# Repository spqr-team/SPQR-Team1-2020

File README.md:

# SPQR1 Team 2020

SPQR1 Team 2020 Robot project repo, we are robot-makers based in ITIS G. Galilei Rome, currently competing in Soccer Lightweight league in RCJ.

Code found in master and mechanics and boards in branch hardware.

We are: 
  Davide Belli  [@DVDSpacca],
  Emanuele Coletta  [@EmaMaker],
  Marco De Amicis [@Morcock] and Siria Sannino  [@u-siri-ous].

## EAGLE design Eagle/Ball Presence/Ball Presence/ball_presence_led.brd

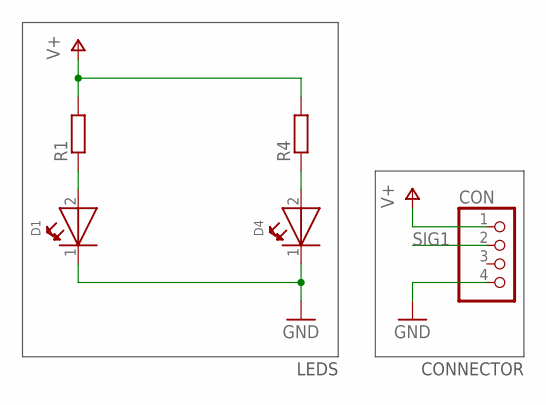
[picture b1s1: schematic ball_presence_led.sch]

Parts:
CON: PINHD-1X4; 1X04
D1, D4: WL-SMTW-150141AS73100-A; 3528-2PIN
R1, R4: R-EU_R0805; R0805

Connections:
GND: CON.4, D1.1 (K), D4.1 (K)
unnamed: D1.2 (A), R1.1
unnamed: D4.2 (A), R4.1
SIG1: CON.2
V+: CON.1, R1.2, R4.2

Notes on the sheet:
LEDS
CONNECTOR

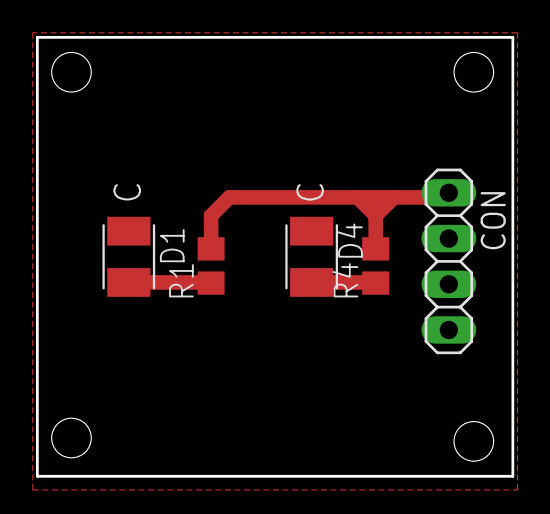
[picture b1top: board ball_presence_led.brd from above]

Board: 2 copper layers, 26.4 x 24.4 mm, 5 parts (0 on the bottom side), 4 nets.

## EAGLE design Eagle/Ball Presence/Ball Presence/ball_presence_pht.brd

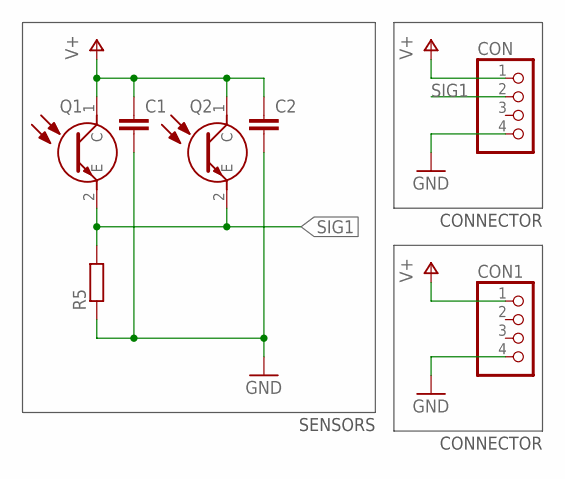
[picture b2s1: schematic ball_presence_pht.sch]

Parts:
C1, C2: C-EUC0805; C0805
CON, CON1: PINHD-1X4; 1X04
Q1, Q2: VEMT2520X01
R5: R-EU_R0805; R0805

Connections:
GND: C1.2, C2.2, CON.4, CON1.4, R5.1
SIG1: CON.2, Q1.2 (E), Q2.2 (E), R5.2
V+: C1.1, C2.1, CON.1, CON1.1, Q1.1 (C), Q2.1 (C)

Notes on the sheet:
SENSORS
CONNECTOR

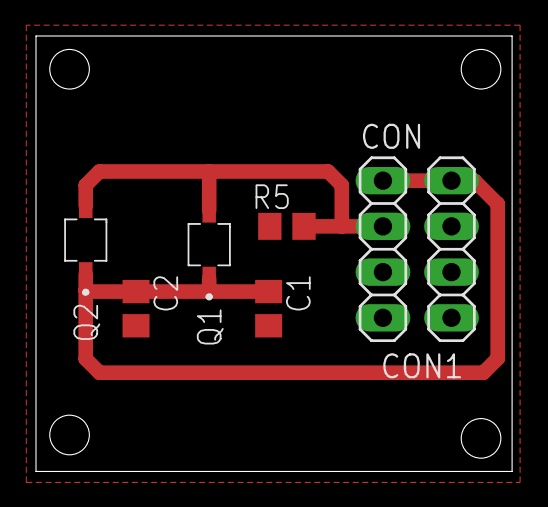
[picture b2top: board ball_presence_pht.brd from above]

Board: 2 copper layers, 26.4 x 24.2 mm, 7 parts (0 on the bottom side), 3 nets.

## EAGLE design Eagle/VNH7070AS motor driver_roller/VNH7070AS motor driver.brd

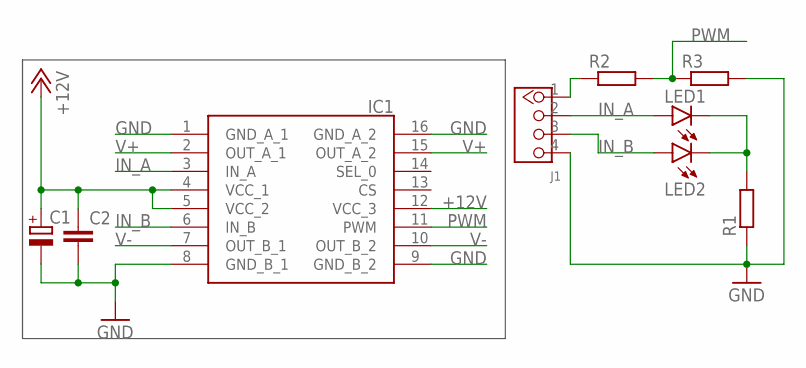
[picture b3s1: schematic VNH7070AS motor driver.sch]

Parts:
C1: CPOL-EUCT7343; CT7343
C2: C-EUC0805; C0805
IC1: VNH7070ASTR; SOIC127P600X175-16N
J1: TWIG_2.0; 2.0_1X4
LED1, LED2: LEDCHIPLED_1206; CHIPLED_1206
R1, R2, R3: R-EU_R0805; R0805

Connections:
+12V: C1.+, C2.1, IC1.4 (VCC_1), IC1.5 (VCC_2), IC1.12 (VCC_3)
GND: C1.-, C2.2, IC1.1 (GND_A_1), IC1.8 (GND_B_1), IC1.9 (GND_B_2), IC1.16 (GND_A_2), J1.4, R1.1, R3.2
IN_A: IC1.3 (IN_A), J1.2, LED1.A
IN_B: IC1.6 (IN_B), J1.3, LED2.A
unnamed: J1.1, R2.1
unnamed: LED1.C, LED2.C, R1.2
PWM: IC1.11 (PWM), R2.2, R3.1
V+: IC1.2 (OUT_A_1), IC1.15 (OUT_A_2)
V-: IC1.7 (OUT_B_1), IC1.10 (OUT_B_2)

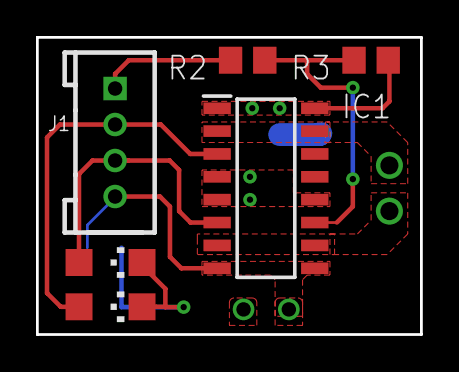
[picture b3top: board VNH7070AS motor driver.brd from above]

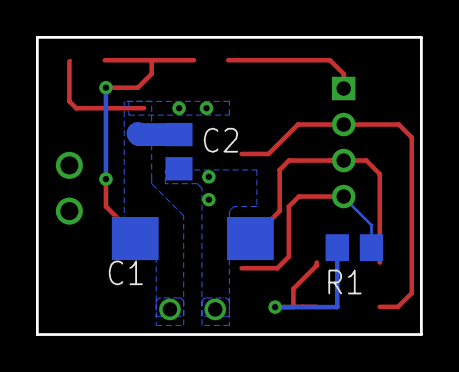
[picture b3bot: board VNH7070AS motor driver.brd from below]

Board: 2 copper layers, 21.3 x 16.5 mm, 9 parts (3 on the bottom side), 9 nets.

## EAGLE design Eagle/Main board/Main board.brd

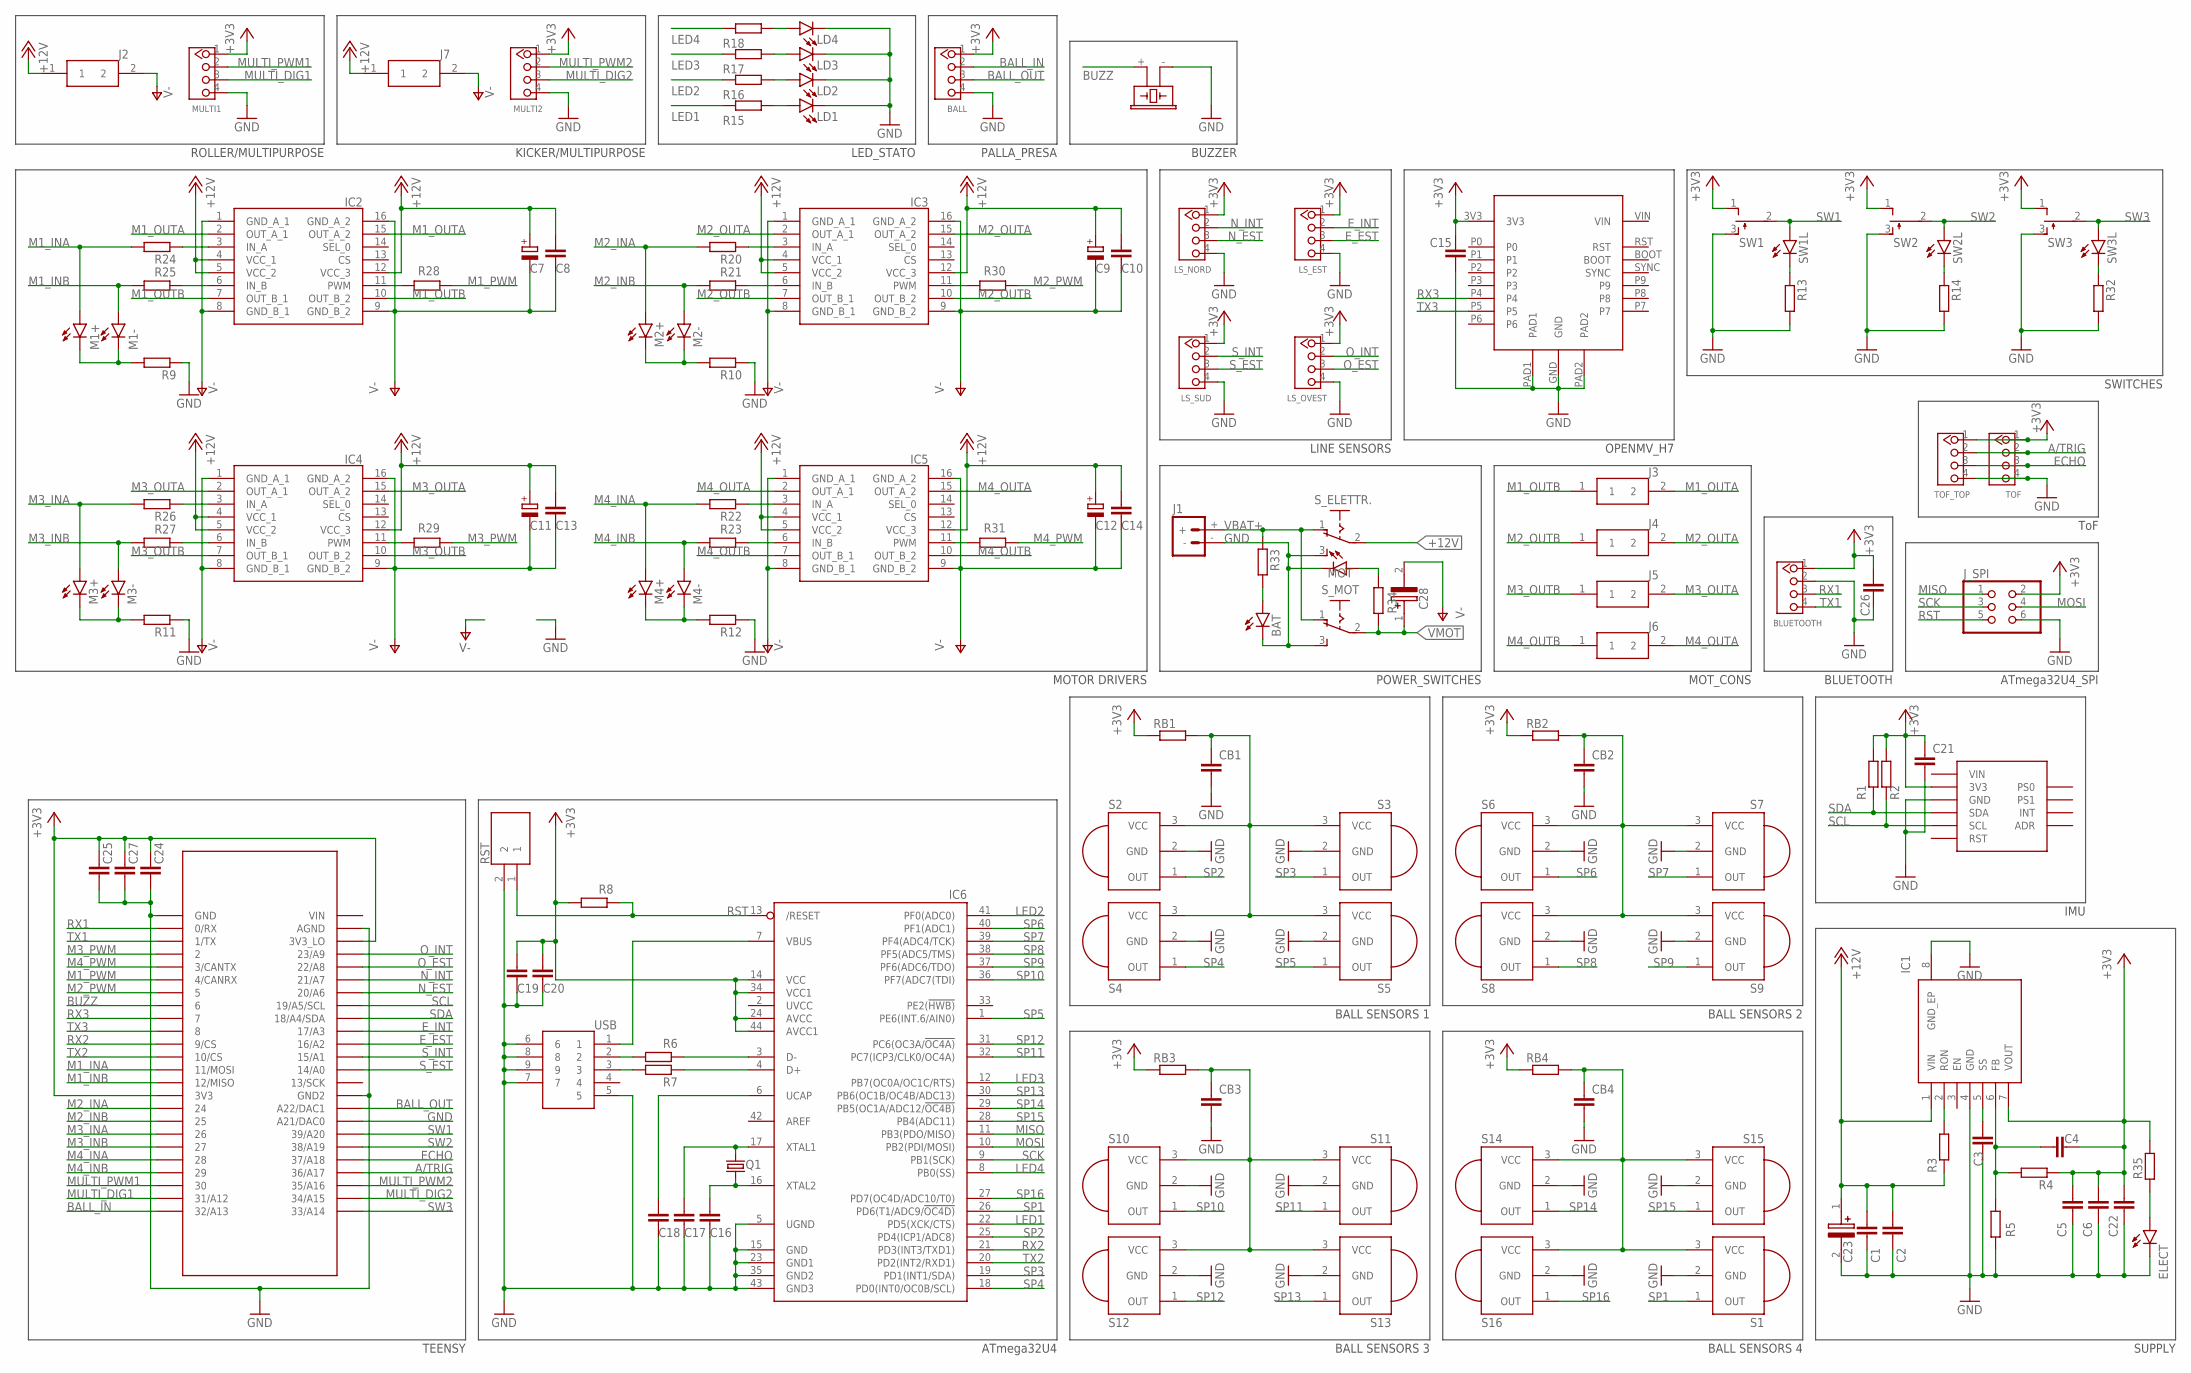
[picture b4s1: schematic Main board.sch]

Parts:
BALL: TWIG_2.0; 2.0_1X4
BAT: LEDCHIPLED_1206; CHIPLED_1206
BLUETOOTH: TWIG_2.0; 2.0_1X4
BUZZER: F/CM12P
C1, C2, C22, C24, C27: 100n; C0805
C3, C4: 22n; C0805
C5, C6: 100u; C1206
C7: 1OOu; PANASONIC_E
C8, C10, C13, C14, C15, C16, C17, C18, C20, C21, C26: 1u; C0805
C9, C11, C12: 100u; PANASONIC_E
C19: 1u; C1206
C23, C28: EEV-FK1C152Q; FKV(H13)
C25: 100n; C1206
CB1, CB2, CB3, CB4: 0.1uF; C0805
ELECT: LEDCHIPLED_1206; CHIPLED_1206
IC1: LMZ14202TZE-ADJ_NOPB; NDW0007A
IC2, IC3, IC4, IC5: VNH7070ASTR; SOIC127P600X175-16N
IC6: ATMEGA32U4-AU; TQFP44
J1: BATTERY_CONN_DEANS; DEANS
J2, J3, J4, J5, J6, J7: 43650-0201; 43650-0200
J_SPI: PINHD-2X3; 2X03
LD1, LD2, LD3, LD4: LEDCHIPLED_1206; CHIPLED_1206
LS_EST: TWIG_2.0; 2.0_1X4
LS_NORD: TWIG_2.0; 2.0_1X4
LS_OVEST: TWIG_2.0; 2.0_1X4
LS_SUD: TWIG_2.0; 2.0_1X4
M1+, M1-, M2+, M2-, M3+, M3-, M4+, M4-: LEDCHIPLED_1206; CHIPLED_1206
MOT: LEDCHIPLED_1206; CHIPLED_1206
MULTI1, MULTI2: TWIG_2.0; 2.0_1X4
Q1: CRYSTALHC49UP; HC49UP
R1, R2: 10k; R0805
R3: 61,9k; R0805
R4: 3,32k; R0805
R5: 1,07k; R0805
R6, R7, R8, R9, R10, R11, R12, R13, R14, R15, R16, R17, R18, R20, R21, R22, R23, R24, R25, R26, R27, R28, R29, R30, R31, R32, R33, R34, R35: R-EU_R0805; R0805
RB1, RB2, RB3, RB4: 22; R0805
RST: KSR231GLFS; KSR
S1, S2, S3, S4, S5, S6, S7, S8, S9, S10, S11, S12, S13, S14, S15, S16: PNA460XM
SW1, SW2, SW3: TL38PO; TL3XPO
SW1L, SW2L, SW3L: LEDCHIPLED_1206; CHIPLED_1206
S_ELETTR.: 255SB
S_MOT: 255SB
TOF: TWIG_2.0; 2.0_1X4
TOF_TOP: TWIG_2.0; 2.0_1X4
U$1: TEENSY_3.5/3.6
U$2: OPENMV_H7
U$4: BNO055
USB: 10104111-0001LF; 101041110001LF

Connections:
+3V3: BALL.1, BLUETOOTH.1, C4.2, C5.1, C6.1, C15.1, C19.1, C20.1, C21.1, C22.1, C24.1, C25.1, C26.1, C27.1, IC1.7 (VOUT), IC6.14 (VCC), IC6.24 (AVCC), IC6.34 (VCC1), IC6.44 (AVCC1), J_SPI.2, LS_EST.1, LS_NORD.1, LS_OVEST.1, LS_SUD.1, MULTI1.1, MULTI2.1, R1.2, R2.2, R4.1, R8.2, R35.2, RB1.1, RB2.1, RB3.1, RB4.1, SW1.1 (O), SW2.1 (O), SW3.1 (O), TOF.1, TOF_TOP.1, U$1.3V3, U$1.3V3_LO, U$2.3V3, U$4.3V3
+12V: C1.1, C2.1, C23.1 (+), IC1.1 (VIN), R3.1, S_ELETTR..2
A/TRIG: TOF.2, TOF_TOP.2, U$1.36/A17
BALL_IN: BALL.2, U$1.32/A13
BALL_OUT: BALL.3, U$1.A22/DAC1
BUZZ: BUZZER.+ (1), U$1.6
ECHO: TOF.3, TOF_TOP.3, U$1.37/A18
E_EST: LS_EST.3, U$1.16/A2
E_INT: LS_EST.2, U$1.17/A3
GND: BALL.4, BAT.C, BLUETOOTH.2, BUZZER.- (2), C1.2, C2.2, C3.2, C5.2, C6.2, C15.2, C16.2, C17.2, C18.2, C19.2, C20.2, C21.2, C22.2, C23.2 (-), C24.2, C25.2, C26.2, C27.2, CB1.2, CB2.2, CB3.2, CB4.2, ELECT.C, IC1.4 (GND), IC1.8 (GND_EP), IC6.5 (UGND), IC6.15 (GND), IC6.23 (GND1), IC6.35 (GND2), IC6.43 (GND3), J1.-, J_SPI.6, LD1.C, LD2.C, LD3.C, LD4.C, LS_EST.4, LS_NORD.4, LS_OVEST.4, LS_SUD.4, MOT.C, MULTI1.4, MULTI2.4, R5.1, R9.1, R10.1, R11.1, R12.1, R13.2, R14.2, R32.2, RST.2, S1.2 (GND), S2.2 (GND), S3.2 (GND), S4.2 (GND), S5.2 (GND), S6.2 (GND), S7.2 (GND), S8.2 (GND), S9.2 (GND), S10.2 (GND), S11.2 (GND), S12.2 (GND), S13.2 (GND), S14.2 (GND), S15.2 (GND), S16.2 (GND), SW1.3 (S), SW2.3 (S), SW3.3 (S), S_ELETTR..3 (S), S_MOT.3 (S), TOF.4, TOF_TOP.4, U$1.21/DAC0 (A21/DAC0), U$1.AGND, U$1.GND, U$1.GND2, U$2.GND, U$2.PAD1, U$2.PAD2, U$4.GND, USB.5, USB.6, USB.7, USB.8, USB.9; also elsewhere on the board
INA_1: IC2.3 (IN_A), R24.1
INA_2: IC3.3 (IN_A), R20.1
INA_3: IC4.3 (IN_A), R26.1
INA_4: IC5.3 (IN_A), R22.1
INB_1: IC2.6 (IN_B), R25.1
INB_2: IC3.6 (IN_B), R21.1
INB_3: IC4.6 (IN_B), R27.1
INB_4: IC5.6 (IN_B), R23.1
LED1: IC6.22 (PD5(XCK/CTS)), R15.1
LED2: IC6.41 (PF0(ADC0)), R16.1
LED3: IC6.12 (PB7(OC0A/OC1C/RTS)), R17.1
LED4: IC6.8 (PB0(SS)), R18.1
M1_INA: M1+.A, R24.2, U$1.11/MOSI
M1_INB: M1-.A, R25.2, U$1.12/MISO
M1_OUTA: IC2.2 (OUT_A_1), IC2.15 (OUT_A_2), J3.2
M1_OUTB: IC2.7 (OUT_B_1), IC2.10 (OUT_B_2), J3.1
M1_PWM: R28.1, U$1.4/CANRX
M2_INA: M2+.A, R20.2, U$1.24
M2_INB: M2-.A, R21.2, U$1.25
M2_OUTA: IC3.2 (OUT_A_1), IC3.15 (OUT_A_2), J4.2
M2_OUTB: IC3.7 (OUT_B_1), IC3.10 (OUT_B_2), J4.1
M2_PWM: R30.1, U$1.5
M3_INA: M3+.A, R26.2, U$1.26
M3_INB: M3-.A, R27.2, U$1.27
M3_OUTA: IC4.2 (OUT_A_1), IC4.15 (OUT_A_2), J5.2
M3_OUTB: IC4.7 (OUT_B_1), IC4.10 (OUT_B_2), J5.1
M3_PWM: R29.1, U$1.2
M4_INA: M4+.A, R22.2, U$1.28
M4_INB: M4-.A, R23.2, U$1.29
M4_OUTA: IC5.2 (OUT_A_1), IC5.15 (OUT_A_2), J6.2
M4_OUTB: IC5.7 (OUT_B_1), IC5.10 (OUT_B_2), J6.1
M4_PWM: R31.1, U$1.3/CANTX
MISO: IC6.11 (PB3(PDO/MISO)), J_SPI.1
MOSI: IC6.10 (PB2(PDI/MOSI)), J_SPI.4
MULTI_DIG1: MULTI1.3, U$1.31/A12
MULTI_DIG2: MULTI2.3, U$1.34/A15
MULTI_PWM1: MULTI1.2, U$1.30
MULTI_PWM2: MULTI2.2, U$1.35/A16
unnamed: IC1.2 (RON), R3.2
unnamed: C4.1, IC1.6 (FB), R4.2, R5.2
unnamed: C3.1, IC1.5 (SS)
unnamed: LD4.A, R18.2
unnamed: C17.1, IC6.17 (XTAL1), Q1.2
unnamed: C16.1, IC6.16 (XTAL2), Q1.1
unnamed: C18.1, IC6.6 (UCAP)
unnamed: IC6.3 (D-), R6.1
unnamed: R6.2, USB.2
unnamed: R7.2, USB.3
unnamed: IC6.4 (D+), R7.1
unnamed: IC6.7 (VBUS), USB.1
unnamed: M2+.C, M2-.C, R10.2
unnamed: M1+.C, M1-.C, R9.2
unnamed: M3+.C, M3-.C, R11.2
unnamed: M4+.C, M4-.C, R12.2
unnamed: R13.1, SW1L.C
unnamed: R14.1, SW2L.C
unnamed: R32.1, SW3L.C
unnamed: LD1.A, R15.2
unnamed: LD2.A, R16.2
unnamed: LD3.A, R17.2
unnamed: BAT.A, R33.2
unnamed: MOT.A, R34.2
unnamed 73: ELECT.A, R35.1; also elsewhere on the board
N_EST: LS_NORD.3, U$1.20/A6
N_INT: LS_NORD.2, U$1.21/A7
O_EST: LS_OVEST.3, U$1.22/A8
O_INT: LS_OVEST.2, U$1.23/A9
POWER_BLOCK_1: CB1.1, RB1.2, S2.3 (VCC), S3.3 (VCC), S4.3 (VCC), S5.3 (VCC)
POWER_BLOCK_2: CB2.1, RB2.2, S6.3 (VCC), S7.3 (VCC), S8.3 (VCC), S9.3 (VCC)
POWER_BLOCK_3: CB3.1, RB3.2, S10.3 (VCC), S11.3 (VCC), S12.3 (VCC), S13.3 (VCC)
POWER_BLOCK_4: CB4.1, RB4.2, S1.3 (VCC), S14.3 (VCC), S15.3 (VCC), S16.3 (VCC)
PWM3: IC4.11 (PWM), R29.2
PWM_1: IC2.11 (PWM), R28.2
PWM_2: IC3.11 (PWM), R30.2
PWM_4: IC5.11 (PWM), R31.2
RST: IC6.13 (/RESET), J_SPI.5, R8.1, RST.1
RX1: BLUETOOTH.3, U$1.0/RX
RX2: IC6.21 (PD3(INT3/TXD1)), U$1.9/CS
RX3: U$1.7, U$2.P4
SCK: IC6.9 (PB1(SCK)), J_SPI.3
SCL: R2.1, U$1.19/A5/SCL, U$4.SCL
SDA: R1.1, U$1.18/A4/SDA, U$4.SDA
SP1: IC6.26 (PD6(T1/ADC9/!OC4D)), S1.1 (OUT)
SP2: IC6.25 (PD4(ICP1/ADC8)), S2.1 (OUT)
SP3: IC6.19 (PD1(INT1/SDA)), S3.1 (OUT)
SP4: IC6.18 (PD0(INT0/OC0B/SCL)), S4.1 (OUT)
SP5: IC6.1 (PE6(INT.6/AIN0)), S5.1 (OUT)
SP6: IC6.40 (PF1(ADC1)), S6.1 (OUT)
SP7: IC6.39 (PF4(ADC4/TCK)), S7.1 (OUT)
SP8: IC6.38 (PF5(ADC5/TMS)), S8.1 (OUT)
SP9: IC6.37 (PF6(ADC6/TDO)), S9.1 (OUT)
SP10: IC6.36 (PF7(ADC7(TDI)), S10.1 (OUT)
SP11: IC6.32 (PC7(ICP3/CLK0/OC4A)), S11.1 (OUT)
SP12: IC6.31 (PC6(OC3A/!OC4A)), S12.1 (OUT)
SP13: IC6.30 (PB6(OC1B/OC4B/ADC13)), S13.1 (OUT)
SP14: IC6.29 (PB5(OC1A/ADC12/!OC4B)), S14.1 (OUT)
SP15: IC6.28 (PB4(ADC11)), S15.1 (OUT)
SP16: IC6.27 (PD7(OC4D/ADC10/T0)), S16.1 (OUT)
SW1: SW1.2, SW1L.A, U$1.39/A20
SW2: SW2.2, SW2L.A, U$1.38/A19
SW3: SW3.2, SW3L.A, U$1.33/A14
S_EST: LS_SUD.3, U$1.14/A0
S_INT: LS_SUD.2, U$1.15/A1
TX1: BLUETOOTH.4, U$1.1/TX
TX2: IC6.20 (PD2(INT2/RXD1)), U$1.10/CS
TX3: U$1.8, U$2.P5
V-: C7.-, C8.2, C9.-, C10.2, C11.-, C12.-, C13.2, C14.2, C28.2 (-), IC2.1 (GND_A_1), IC2.8 (GND_B_1), IC2.9 (GND_B_2), IC2.16 (GND_A_2), IC3.1 (GND_A_1), IC3.8 (GND_B_1), IC3.9 (GND_B_2), IC3.16 (GND_A_2), IC4.1 (GND_A_1), IC4.8 (GND_B_1), IC4.9 (GND_B_2), IC4.16 (GND_A_2), IC5.1 (GND_A_1), IC5.8 (GND_B_1), IC5.9 (GND_B_2), IC5.16 (GND_A_2), J2.2, J7.2
VBAT+: J1.+, R33.1, S_ELETTR..1 (O), S_MOT.1 (O)
VMOT: C7.+, C8.1, C9.+, C10.1, C11.+, C12.+, C13.1, C14.1, C28.1 (+), IC2.4 (VCC_1), IC2.5 (VCC_2), IC2.12 (VCC_3), IC3.4 (VCC_1), IC3.5 (VCC_2), IC3.12 (VCC_3), IC4.4 (VCC_1), IC4.5 (VCC_2), IC4.12 (VCC_3), IC5.4 (VCC_1), IC5.5 (VCC_2), IC5.12 (VCC_3), J2.1, J7.1, R34.1, S_MOT.2

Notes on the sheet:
TEENSY
IMU
SUPPLY
POWER_SWITCHES
BALL SENSORS 1
BALL SENSORS 2
BALL SENSORS 3
BALL SENSORS 4
LINE SENSORS
MOTOR DRIVERS
OPENMV_H7
ATmega32U4
ATmega32U4_SPI
SWITCHES
BUZZER
LED_STATO
MOT_CONS
BLUETOOTH
ToF
ROLLER/MULTIPURPOSE
KICKER/MULTIPURPOSE
PALLA_PRESA

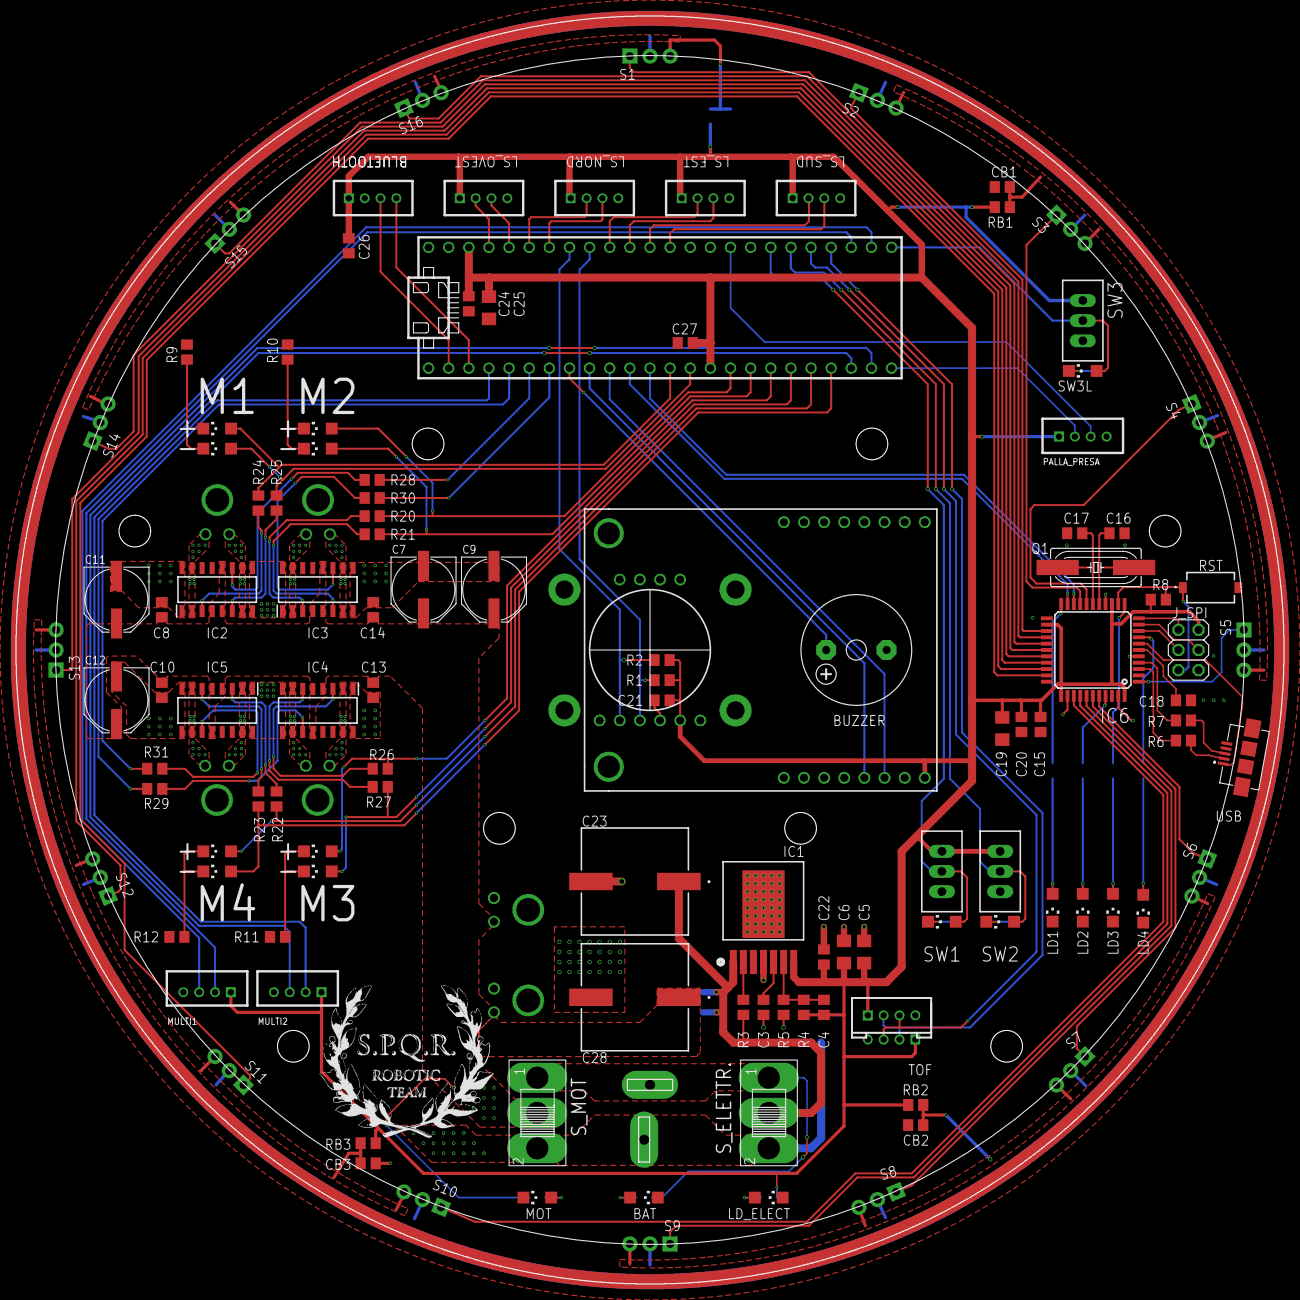
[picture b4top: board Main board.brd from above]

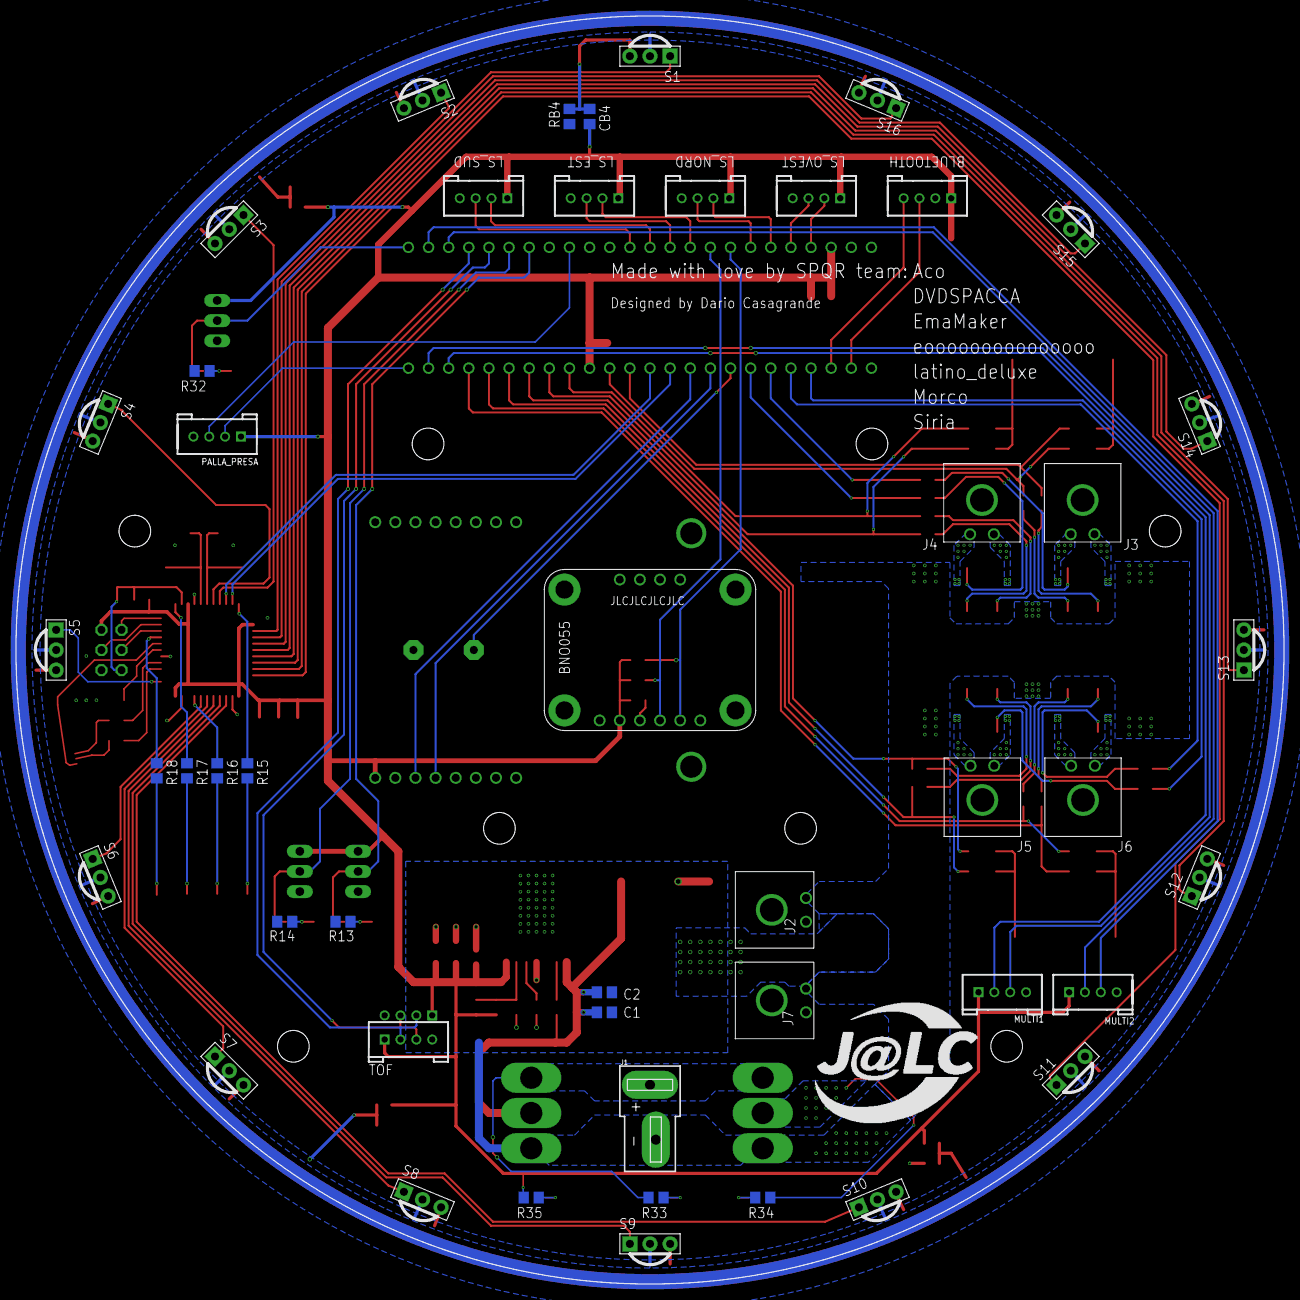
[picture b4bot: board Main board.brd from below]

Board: 2 copper layers, 160.0 x 160.0 mm, 140 parts (47 on the bottom side), 119 nets.

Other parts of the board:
LD_ELECT: CHIPLED_1206

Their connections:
GND: LD_ELECT.C; also elsewhere on the board
unnamed 73: LD_ELECT.A; also elsewhere on the board

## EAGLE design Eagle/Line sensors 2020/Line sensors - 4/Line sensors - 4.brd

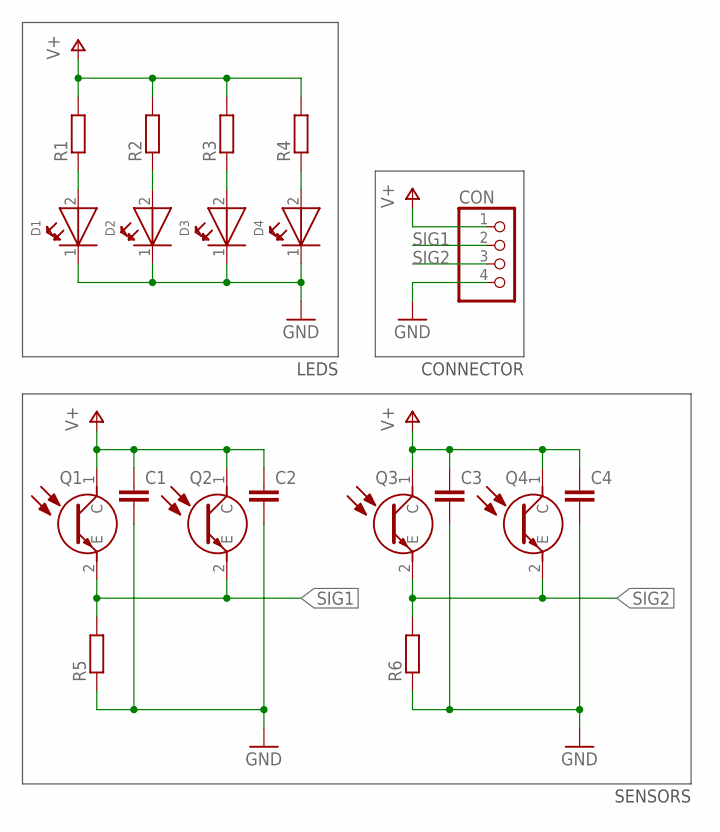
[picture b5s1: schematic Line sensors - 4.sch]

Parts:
C1, C2, C3, C4: C-EUC0805; C0805
CON: PINHD-1X4; 1X04
D1, D2, D3, D4: WL-SMTW-150141AS73100-A; 3528-2PIN
Q1, Q2, Q3, Q4: VEMT2520X01
R1, R2, R3, R4, R5, R6: R-EU_R0805; R0805

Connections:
GND: C1.2, C2.2, C3.2, C4.2, CON.4, D1.1 (K), D2.1 (K), D3.1 (K), D4.1 (K), R5.1, R6.1; also elsewhere on the board
unnamed: D1.2 (A), R1.1
unnamed: D2.2 (A), R2.1
unnamed: D3.2 (A), R3.1
unnamed: D4.2 (A), R4.1
SIG1: CON.2, Q1.2 (E), Q2.2 (E), R5.2; also elsewhere on the board
SIG2: CON.3, Q3.2 (E), Q4.2 (E), R6.2; also elsewhere on the board
V+: C1.1, C2.1, C3.1, C4.1, CON.1, Q1.1 (C), Q2.1 (C), Q3.1 (C), Q4.1 (C), R1.2, R2.2, R3.2, R4.2; also elsewhere on the board

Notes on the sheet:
SENSORS
LEDS
CONNECTOR

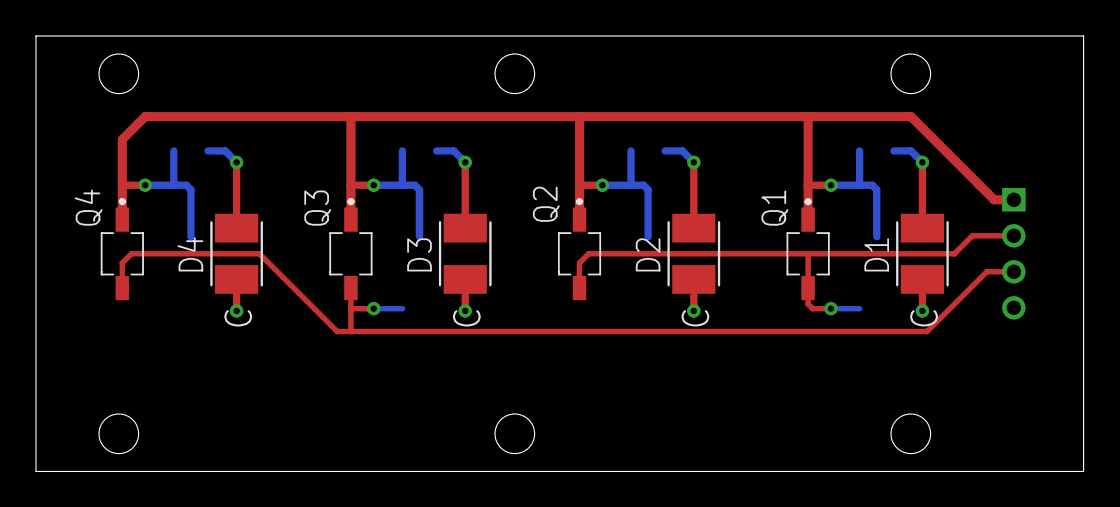
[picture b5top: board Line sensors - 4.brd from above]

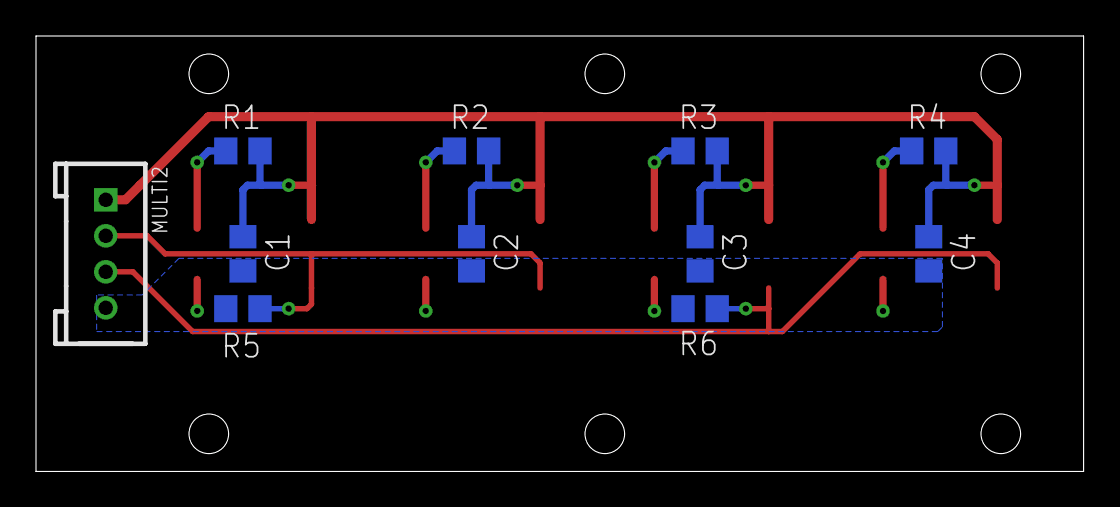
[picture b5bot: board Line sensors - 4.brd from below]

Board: 2 copper layers, 58.2 x 24.2 mm, 19 parts (11 on the bottom side), 8 nets.

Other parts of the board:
MULTI2: TWIG_2.0; 2.0_1X4

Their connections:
GND: MULTI2.4; also elsewhere on the board
SIG1: MULTI2.2; also elsewhere on the board
SIG2: MULTI2.3; also elsewhere on the board
V+: MULTI2.1; also elsewhere on the board

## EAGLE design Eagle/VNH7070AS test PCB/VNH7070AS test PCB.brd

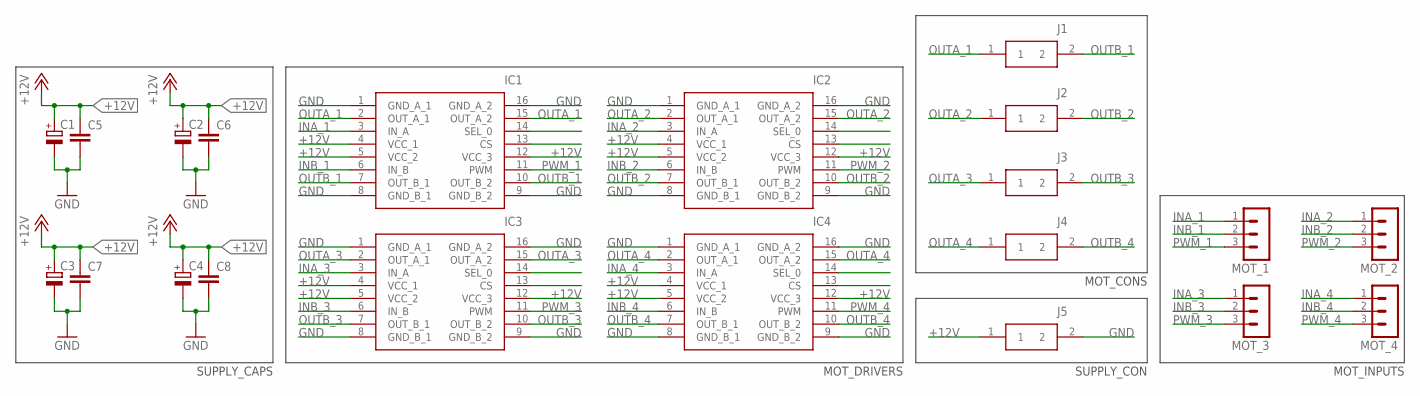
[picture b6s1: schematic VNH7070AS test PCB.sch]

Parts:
C1, C2, C3, C4: 220uF; E3,5-8
C5, C6, C7, C8: 100nF; C1206
IC1, IC2, IC3, IC4: VNH7070ASTR; SOIC127P600X175-16N
J1, J2, J3, J4, J5: 70553-0001; SHDRRA2W109P0_254_1X2_762X1359
MOT_1, MOT_2, MOT_3, MOT_4: MA03-1

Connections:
+12V: C1.+, C2.+, C3.+, C4.+, C5.1, C6.1, C7.1, C8.1, IC1.4 (VCC_1), IC1.5 (VCC_2), IC1.12 (VCC_3), IC2.4 (VCC_1), IC2.5 (VCC_2), IC2.12 (VCC_3), IC3.4 (VCC_1), IC3.5 (VCC_2), IC3.12 (VCC_3), IC4.4 (VCC_1), IC4.5 (VCC_2), IC4.12 (VCC_3), J5.1
GND: C1.-, C2.-, C3.-, C4.-, C5.2, C6.2, C7.2, C8.2, IC1.1 (GND_A_1), IC1.8 (GND_B_1), IC1.9 (GND_B_2), IC1.16 (GND_A_2), IC2.1 (GND_A_1), IC2.8 (GND_B_1), IC2.9 (GND_B_2), IC2.16 (GND_A_2), IC3.1 (GND_A_1), IC3.8 (GND_B_1), IC3.9 (GND_B_2), IC3.16 (GND_A_2), IC4.1 (GND_A_1), IC4.8 (GND_B_1), IC4.9 (GND_B_2), IC4.16 (GND_A_2), J5.2
INA_1: IC1.3 (IN_A), MOT_1.1
INA_2: IC2.3 (IN_A), MOT_2.1
INA_3: IC3.3 (IN_A), MOT_3.1
INA_4: IC4.3 (IN_A), MOT_4.1
INB_1: IC1.6 (IN_B), MOT_1.2
INB_2: IC2.6 (IN_B), MOT_2.2
INB_3: IC3.6 (IN_B), MOT_3.2
INB_4: IC4.6 (IN_B), MOT_4.2
OUTA_1: IC1.2 (OUT_A_1), IC1.15 (OUT_A_2), J1.1
OUTA_2: IC2.2 (OUT_A_1), IC2.15 (OUT_A_2), J2.1
OUTA_3: IC3.2 (OUT_A_1), IC3.15 (OUT_A_2), J3.1
OUTA_4: IC4.2 (OUT_A_1), IC4.15 (OUT_A_2), J4.1
OUTB_1: IC1.7 (OUT_B_1), IC1.10 (OUT_B_2), J1.2
OUTB_2: IC2.7 (OUT_B_1), IC2.10 (OUT_B_2), J2.2
OUTB_3: IC3.7 (OUT_B_1), IC3.10 (OUT_B_2), J3.2
OUTB_4: IC4.7 (OUT_B_1), IC4.10 (OUT_B_2), J4.2
PWM_1: IC1.11 (PWM), MOT_1.3
PWM_2: IC2.11 (PWM), MOT_2.3
PWM_3: IC3.11 (PWM), MOT_3.3
PWM_4: IC4.11 (PWM), MOT_4.3

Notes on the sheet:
SUPPLY_CAPS
MOT_DRIVERS
MOT_CONS
SUPPLY_CON
MOT_INPUTS

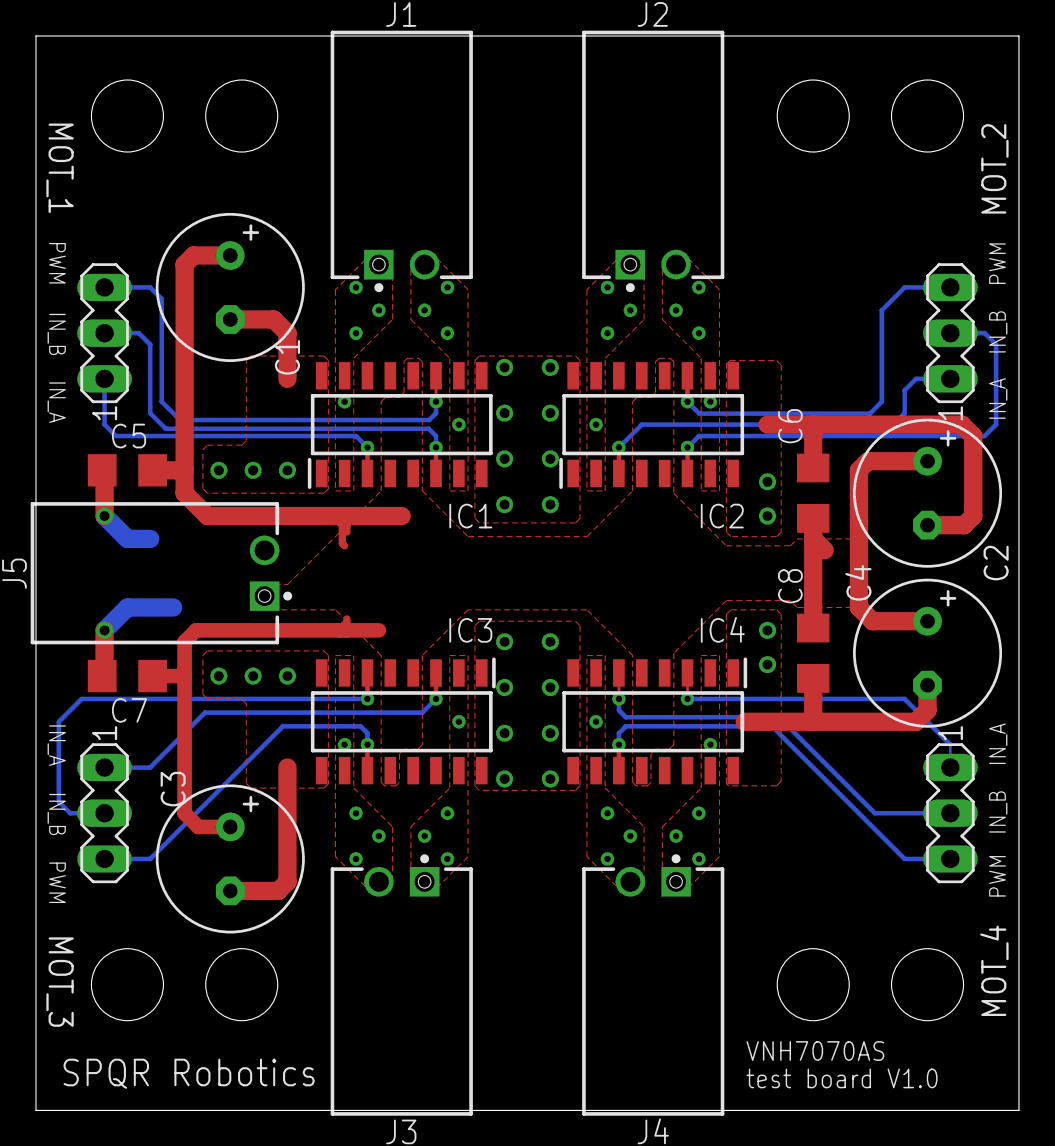
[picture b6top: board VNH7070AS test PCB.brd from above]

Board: 2 copper layers, 54.6 x 59.7 mm, 21 parts (0 on the bottom side), 22 nets.

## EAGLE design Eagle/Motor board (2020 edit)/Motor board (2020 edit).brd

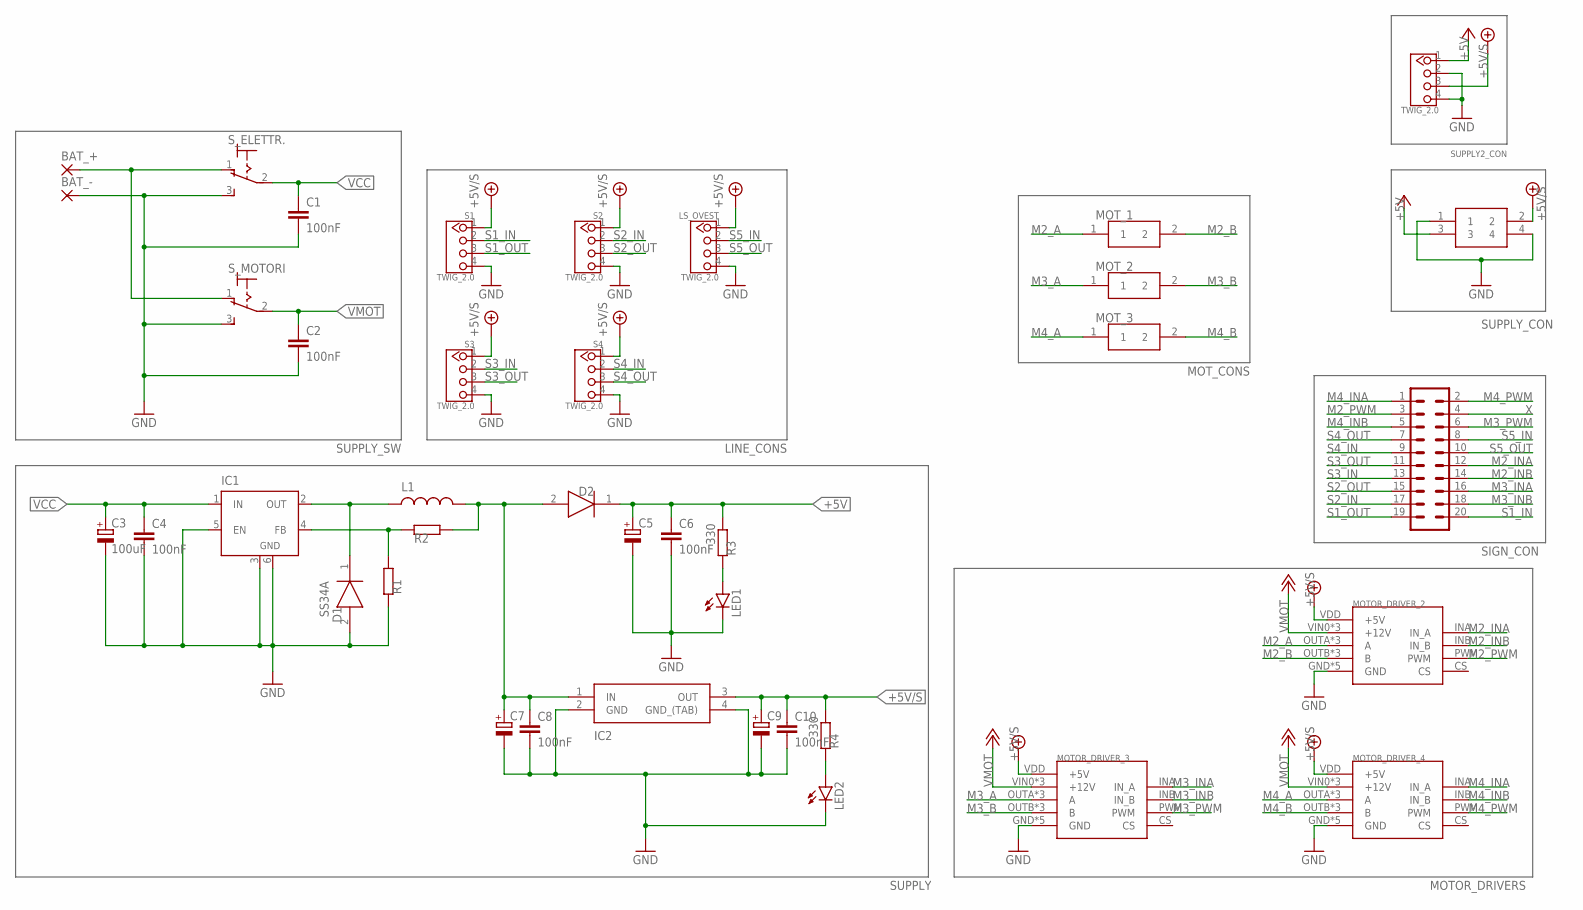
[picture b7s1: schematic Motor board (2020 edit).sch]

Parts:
BAT_+: 3,81/1,4
BAT_-: 3,81/1,4
C1, C2, C4, C6, C8, C10: 100nF; C1206
C3: 100uF; CT7343
C5, C7, C9: CPOL-EUE; PANASONIC_E
D1: SS34A; DIOM5026X262N
D2: SE20FG-M3_H; SODFL3718X108N
IC1: LM2596S; TO263-5
IC2: LM2940CS-5.0_NOPB; TO254P1435X464-4N
L1: 47uH; MSS1260
LED1, LED2: LEDSML1206; SML1206
LS_OVEST: TWIG_2.0; 2.0_1X4
MOTOR_DRIVER_2, MOTOR_DRIVER_3, MOTOR_DRIVER_4: VNH5019
MOT_1, MOT_2, MOT_3: 43650-0201; 43650-0200
R1, R3, R4: 330; R1206
R2: 1,2k; R1206
S1, S2, S3, S4: TWIG_2.0; 2.0_1X4
SIGN_CON: 20V
SUPPLY2_CON: TWIG_2.0; 2.0_1X4
SUPPLY_CON: 39-28-1043
S_ELETTR.: 320-916
S_MOTORI: 320-916

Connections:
5.7V-DIRAMAZIONE2: C7.+, C8.1, D2.2 (A), IC2.1 (IN), L1.P$1, R2.1
+5V: C5.+, C6.1, D2.1 (K), R3.1, SUPPLY2_CON.1, SUPPLY_CON.3
+5V/S: C9.+, C10.1, IC2.3 (OUT), LS_OVEST.1, MOTOR_DRIVER_2.VDD (+5V), MOTOR_DRIVER_3.VDD (+5V), MOTOR_DRIVER_4.VDD (+5V), R4.1, S1.1, S2.1, S3.1, S4.1, SUPPLY2_CON.3, SUPPLY_CON.2
GND: BAT_-.1, C1.2, C2.2, C3.-, C4.2, C5.-, C6.2, C7.-, C8.2, C9.-, C10.2, D1.2 (A), IC1.3 (GND), IC1.5 (EN), IC1.6 (GND), IC2.2 (GND), IC2.4 (GND_(TAB)), LED1.C, LED2.C, LS_OVEST.4, MOTOR_DRIVER_2.GND, MOTOR_DRIVER_2.GND0 (GND), MOTOR_DRIVER_2.GND1 (GND), MOTOR_DRIVER_2.GND2 (GND), MOTOR_DRIVER_2.GND3 (GND), MOTOR_DRIVER_3.GND, MOTOR_DRIVER_3.GND0 (GND), MOTOR_DRIVER_3.GND1 (GND), MOTOR_DRIVER_3.GND2 (GND), MOTOR_DRIVER_3.GND3 (GND), MOTOR_DRIVER_4.GND, MOTOR_DRIVER_4.GND0 (GND), MOTOR_DRIVER_4.GND1 (GND), MOTOR_DRIVER_4.GND2 (GND), MOTOR_DRIVER_4.GND3 (GND), R1.1, S1.4, S2.4, S3.4, S4.4, SUPPLY2_CON.2, SUPPLY2_CON.4, SUPPLY_CON.1, SUPPLY_CON.4, S_ELETTR..3 (S), S_MOTORI.3 (S)
M2_A: MOTOR_DRIVER_2.OUTA (A), MOTOR_DRIVER_2.OUTA2 (A), MOTOR_DRIVER_2.OUTA3 (A), MOT_1.1
M2_B: MOTOR_DRIVER_2.OUTB (B), MOTOR_DRIVER_2.OUTB1 (B), MOTOR_DRIVER_2.OUTB3 (B), MOT_1.2
M2_INA: MOTOR_DRIVER_2.INA (IN_A), SIGN_CON.12
M2_INB: MOTOR_DRIVER_2.INB (IN_B), SIGN_CON.14
M2_PWM: MOTOR_DRIVER_2.PWM, SIGN_CON.3
M3_A: MOTOR_DRIVER_3.OUTA (A), MOTOR_DRIVER_3.OUTA2 (A), MOTOR_DRIVER_3.OUTA3 (A), MOT_2.1
M3_B: MOTOR_DRIVER_3.OUTB (B), MOTOR_DRIVER_3.OUTB1 (B), MOTOR_DRIVER_3.OUTB3 (B), MOT_2.2
M3_INA: MOTOR_DRIVER_3.INA (IN_A), SIGN_CON.16
M3_INB: MOTOR_DRIVER_3.INB (IN_B), SIGN_CON.18
M3_PWM: MOTOR_DRIVER_3.PWM, SIGN_CON.6
M4_A: MOTOR_DRIVER_4.OUTA (A), MOTOR_DRIVER_4.OUTA2 (A), MOTOR_DRIVER_4.OUTA3 (A), MOT_3.1
M4_B: MOTOR_DRIVER_4.OUTB (B), MOTOR_DRIVER_4.OUTB1 (B), MOTOR_DRIVER_4.OUTB3 (B), MOT_3.2
M4_INA: MOTOR_DRIVER_4.INA (IN_A), SIGN_CON.1
M4_INB: MOTOR_DRIVER_4.INB (IN_B), SIGN_CON.5
M4_PWM: MOTOR_DRIVER_4.PWM, SIGN_CON.2
unnamed: BAT_+.1, S_ELETTR..1 (O), S_MOTORI.1 (O)
unnamed: LED2.A, R4.2
unnamed: LED1.A, R3.2
unnamed: D1.1 (K), IC1.2 (OUT), L1.P$2
unnamed: IC1.4 (FB), R1.2, R2.2
S1_IN: S1.2, SIGN_CON.20
S1_OUT: S1.3, SIGN_CON.19
S2_IN: S2.2, SIGN_CON.17
S2_OUT: S2.3, SIGN_CON.15
S3_IN: S3.2, SIGN_CON.13
S3_OUT: S3.3, SIGN_CON.11
S4_IN: S4.2, SIGN_CON.9
S4_OUT: S4.3, SIGN_CON.7
S5_IN: LS_OVEST.2, SIGN_CON.8
S5_OUT: LS_OVEST.3, SIGN_CON.10
VCC: C1.1, C3.+, C4.1, IC1.1 (IN), S_ELETTR..2
VMOT: C2.1, MOTOR_DRIVER_2.VIN0 (+12V), MOTOR_DRIVER_2.VIN1 (+12V), MOTOR_DRIVER_2.VIN2 (+12V), MOTOR_DRIVER_3.VIN0 (+12V), MOTOR_DRIVER_3.VIN1 (+12V), MOTOR_DRIVER_3.VIN2 (+12V), MOTOR_DRIVER_4.VIN0 (+12V), MOTOR_DRIVER_4.VIN1 (+12V), MOTOR_DRIVER_4.VIN2 (+12V), S_MOTORI.2
X: SIGN_CON.4

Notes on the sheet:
SUPPLY_SW
SUPPLY
LINE_CONS
MOT_CONS
MOTOR_DRIVERS

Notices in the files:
parts and their libraries:
Wurth_Elektronik_Optoelectronics_rev15b: Copyright: Würth Elektronik
SparkFun-Connectors: Licensing: Creative Commons ShareAlike 4.0 International - https://creativecommons.org/licenses/by-sa/4.0
